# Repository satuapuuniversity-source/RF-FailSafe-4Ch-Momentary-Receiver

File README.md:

This project is a smart RF receiver board made for things like quiz buzzers, remote switches, or simple automation systems.

Normally, RF receivers can have a problem:
👉 if the signal suddenly stops, the output can get “stuck” ON.
That’s bad, especially in real applications.

So I fixed that.

This board uses a small logic chip (74HC08) to make sure:
✔ the output turns ON only when a signal is actually present
✔ and turns OFF instantly when the signal is gone

So everything works clean and momentary—just like pressing a button.

Another cool thing is the RCA outputs.
They work like simple switches (dry contact), not powered outputs.

👉 That means you can safely connect this board to other systems without worrying about voltage mismatch.

Each channel also has:
💡 a small LED
🔁 a sensing loop (10k resistor)

So you can see if your external device is connected and working. Super helpful during setup.

For power, it runs on a single 18650 battery, and a boost converter keeps everything stable at 5V.
So it’s portable and reliable.

And the PCB?
Designed in KiCad with clear labels, so it’s easy to install and use, even if you're not an expert.

👉 In short:
This is a safe, reliable, no-glitch RF receiver that behaves exactly how you expect—no stuck signals, no confusion.

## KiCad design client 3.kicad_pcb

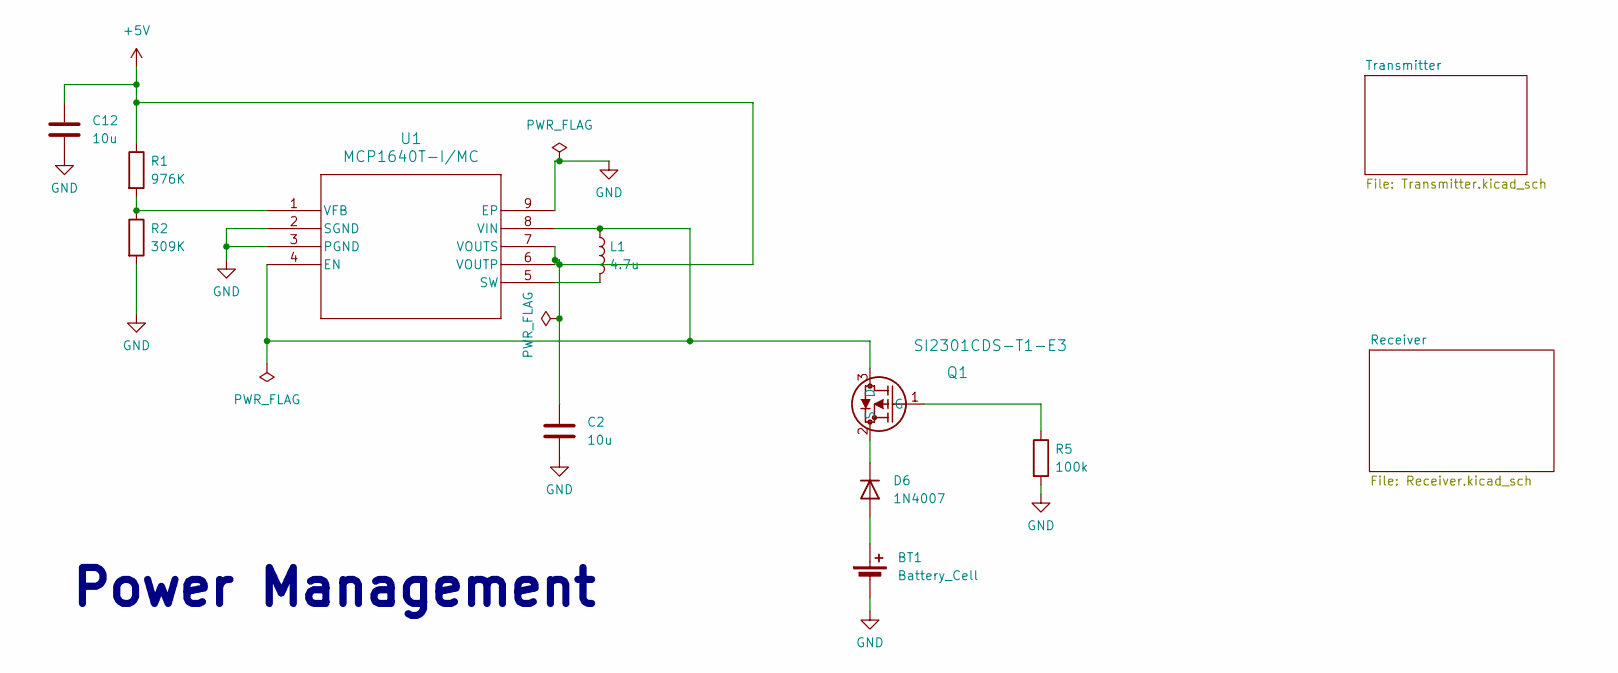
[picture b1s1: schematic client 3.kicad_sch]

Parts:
BT1: Battery_Cell; BatteryHolder_Keystone_1042_1x18650
C2, C12: 10u; C_0805_2012Metric
D6: 1N4007; D_DO-41_SOD81_P10.16mm_Horizontal
L1: 4.7u; R_0805_2012Metric
Q1: SI2301CDS-T1-E3; SOT-23
R1: 976K; R_0805_2012Metric
R2: 309K; R_0805_2012Metric
R5: 100k; R_0805_2012Metric
U1: MCP1640T-I/MC; DFN-8-1EP_2x3mm_P0.5mm_EP0.61x2.2mm

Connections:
GND: BT1.2 (-), C2.2, C12.2, R2.2, R5.2, U1.2 (SGND), U1.3 (PGND), U1.9 (EP); also elsewhere on the board
unnamed: BT1.1 (+), D6.2 (A)
unnamed: D6.1 (K), Q1.2 (S)
unnamed: L1.1, Q1.3 (D), U1.4 (EN), U1.8 (VIN)
unnamed: Q1.1 (G), R5.1
unnamed: L1.2, U1.5 (SW)
unnamed: R1.2, R2.1, U1.1 (VFB)

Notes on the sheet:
Power Management

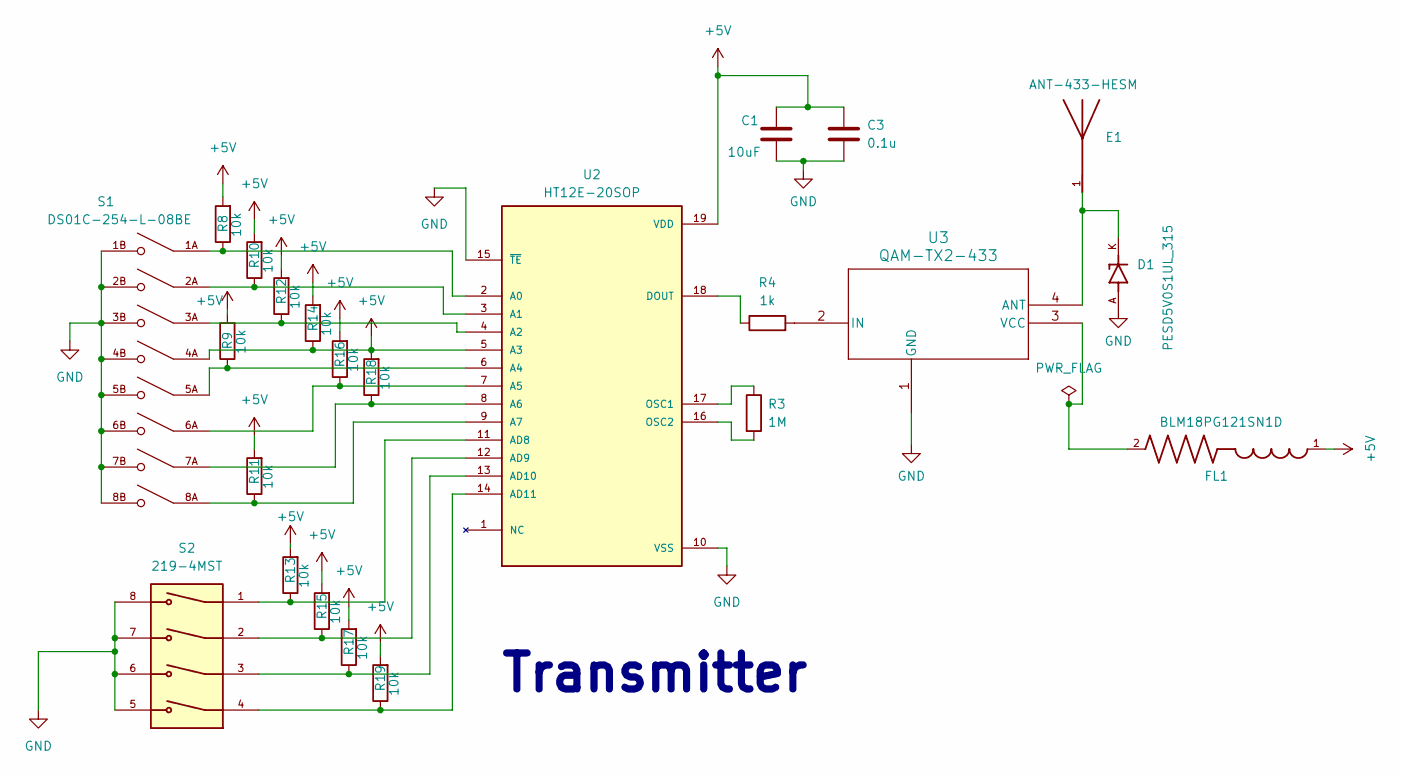
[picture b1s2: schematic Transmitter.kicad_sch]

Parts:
C1: 10uF; C_0805_2012Metric
C3: 0.1u; C_0603_1608Metric
D1: PESD5V0S1UL_315; DIO_PESD5V0S1UL_315
E1: ANT-433-HESM; XDCR_ANT-433-HESM; PARTREV B
FL1: BLM18PG121SN1D; BEADC1608X95N
R3: 1M; R_0805_2012Metric
R4: 1k; R_0805_2012Metric
R8, R9, R10, R11, R12, R13, R14, R15, R16, R17, R18, R19: 10k; R_0805_2012Metric
S1: DS01C-254-L-08BE; SW_DS01C-254-L-08BE; PARTREV 1.0
S2: 219-4MST; SW_219-4MST; PARTREV C
U2: HT12E-20SOP; SOP127P1032X264-20N; PARTREV 1.1
U3: QAM-TX2-433; QAM-TX2-433_RFS

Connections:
GND: C1.2, C3.2, D1.A, S1.1B, S1.2B, S1.3B, S1.4B, S1.5B, S1.6B, S1.7B, S1.8B, S2.5, S2.6, S2.7, S2.8, U2.10 (VSS), U2.15 (~TE), U3.1 (GND); also elsewhere on the board
unnamed: R8.1, S1.1A, U2.2 (A0)
unnamed: R10.1, S1.2A, U2.3 (A1)
unnamed: R12.1, S1.3A, U2.4 (A2)
unnamed: R9.1, S1.5A, U2.6 (A4)
unnamed: R16.1, S1.6A, U2.7 (A5)
unnamed: R18.1, S1.7A, U2.8 (A6)
unnamed: R11.1, S1.8A, U2.9 (A7)
unnamed: R13.1, S2.1, U2.11 (AD8)
unnamed: R15.1, S2.2, U2.12 (AD9)
unnamed: R17.1, S2.3, U2.13 (AD10)
unnamed: R19.1, S2.4, U2.14 (AD11)
unnamed: R4.1, U2.18 (DOUT)
unnamed: R3.1, U2.17 (OSC1)
unnamed: R3.2, U2.16 (OSC2)
unnamed: D1.K, E1.1, U3.4 (ANT)
unnamed: R4.2, U3.2 (IN)
unnamed: FL1.2, U3.3 (VCC)

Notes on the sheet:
Transmitter

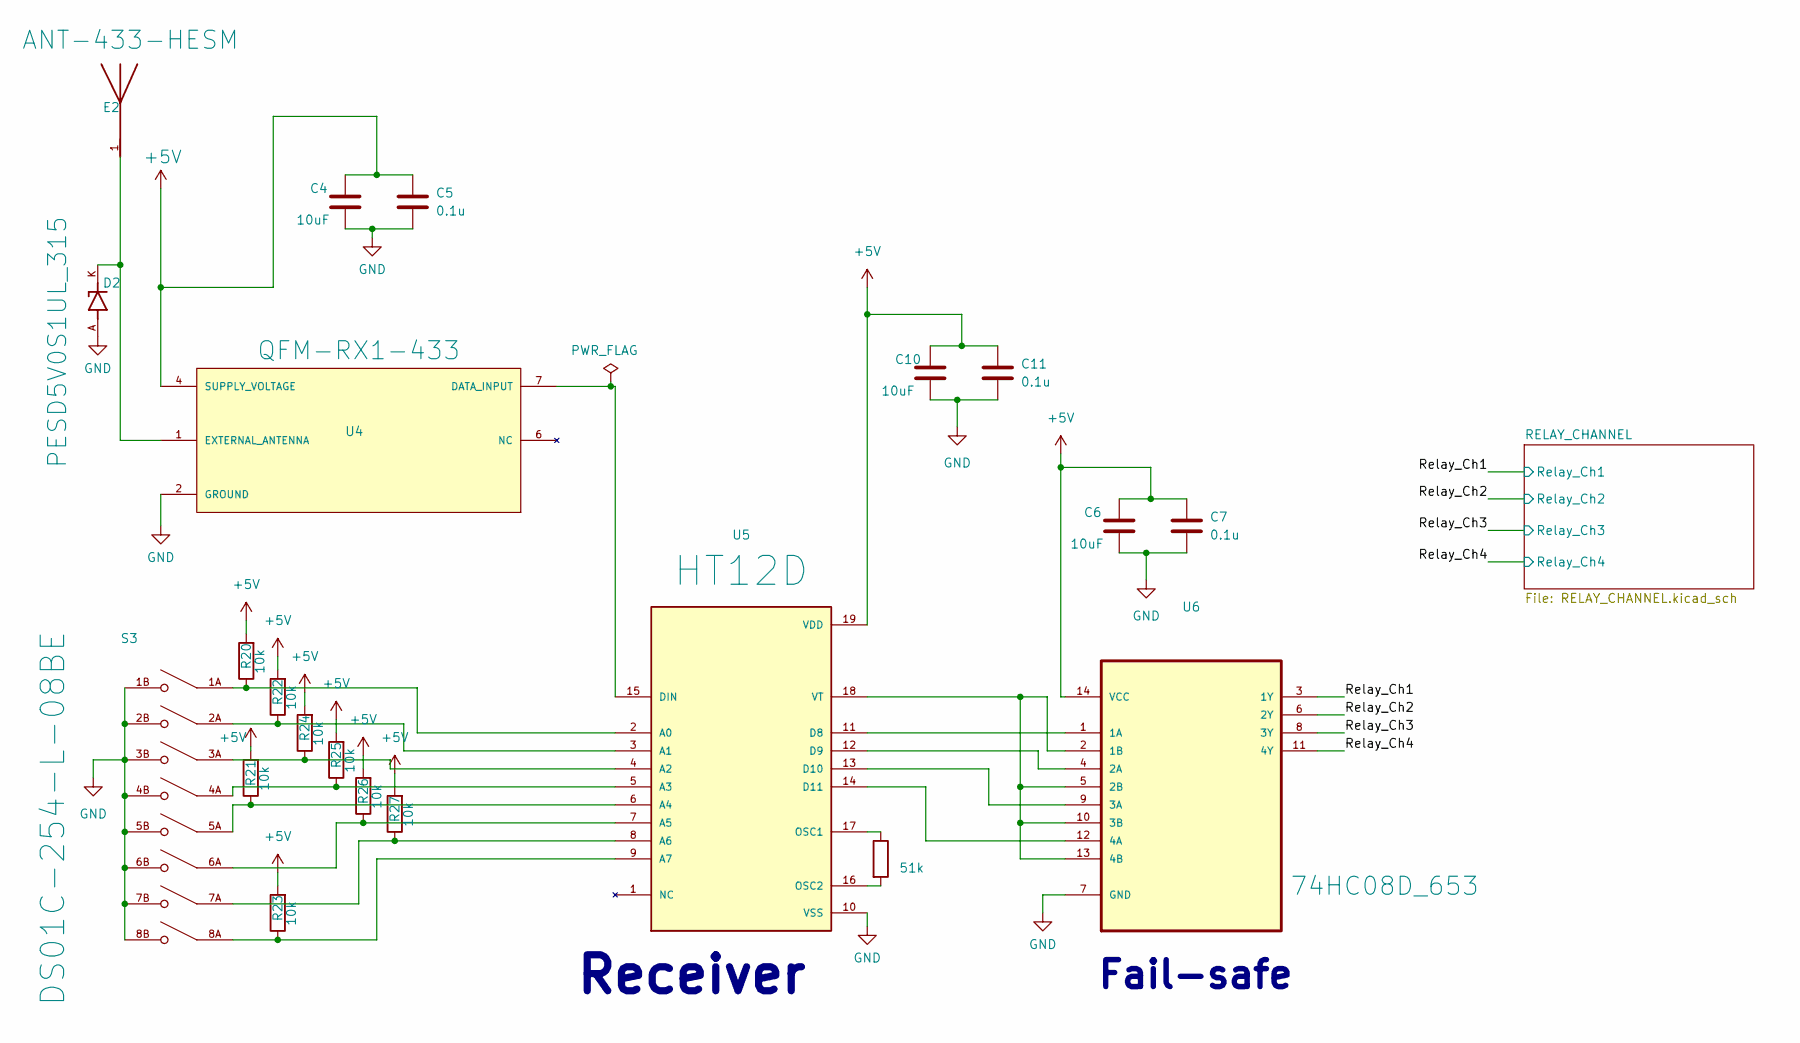
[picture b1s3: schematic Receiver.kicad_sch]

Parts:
C4, C6, C10: 10uF; C_0805_2012Metric
C5, C7, C11: 0.1u; C_0603_1608Metric
D2: PESD5V0S1UL_315; DIO_PESD5V0S1UL_315
E2: ANT-433-HESM; XDCR_ANT-433-HESM; PARTREV B
R6: 51k; R_0805_2012Metric
R20, R21, R22, R23, R24, R25, R26, R27: 10k; R_0805_2012Metric
S3: DS01C-254-L-08BE; SW_DS01C-254-L-08BE; PARTREV 1.0
U4: QFM-RX1-433; MODULE_QFM-RX1-433; PARTREV March 14
U5: HT12D; SOP127P1032X264-20N; PARTREV 1.4
U6: 74HC08D_653; SOIC127P600X175-14N; MPN 74HC08D,653

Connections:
/Receiver/Relay_Ch1: U6.3 (1Y); also elsewhere on the board
/Receiver/Relay_Ch2: U6.6 (2Y); also elsewhere on the board
/Receiver/Relay_Ch3: U6.8 (3Y); also elsewhere on the board
/Receiver/Relay_Ch4: U6.11 (4Y); also elsewhere on the board
GND: C4.2, C5.2, C6.2, C7.2, C10.2, C11.2, D2.A, S3.1B, S3.2B, S3.3B, S3.4B, S3.5B, S3.6B, S3.7B, S3.8B, U4.2 (GROUND), U4.3 (GROUND), U4.8 (GROUND), U5.10 (VSS), U6.7 (GND); also elsewhere on the board
unnamed: U4.7 (DATA_INPUT), U5.15 (DIN)
unnamed: D2.K, E2.1, U4.1 (EXTERNAL_ANTENNA)
unnamed: R20.1, S3.1A, U5.2 (A0)
unnamed: R22.1, S3.2A, U5.3 (A1)
unnamed: R24.1, S3.3A, U5.4 (A2)
unnamed: R25.1, S3.4A, U5.5 (A3)
unnamed: R21.1, S3.5A, U5.6 (A4)
unnamed: R26.1, S3.6A, U5.7 (A5)
unnamed: R27.1, S3.7A, U5.8 (A6)
unnamed: R23.1, S3.8A, U5.9 (A7)
unnamed: U5.11 (D8), U6.1 (1A)
unnamed: U5.12 (D9), U6.4 (2A)
unnamed: U5.13 (D10), U6.9 (3A)
unnamed: U5.14 (D11), U6.12 (4A)
unnamed: R6.1, U5.17 (OSC1)
unnamed: R6.2, U5.16 (OSC2)
unnamed: U5.18 (VT), U6.2 (1B), U6.5 (2B), U6.10 (3B), U6.13 (4B)

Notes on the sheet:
Fail-safe
Receiver

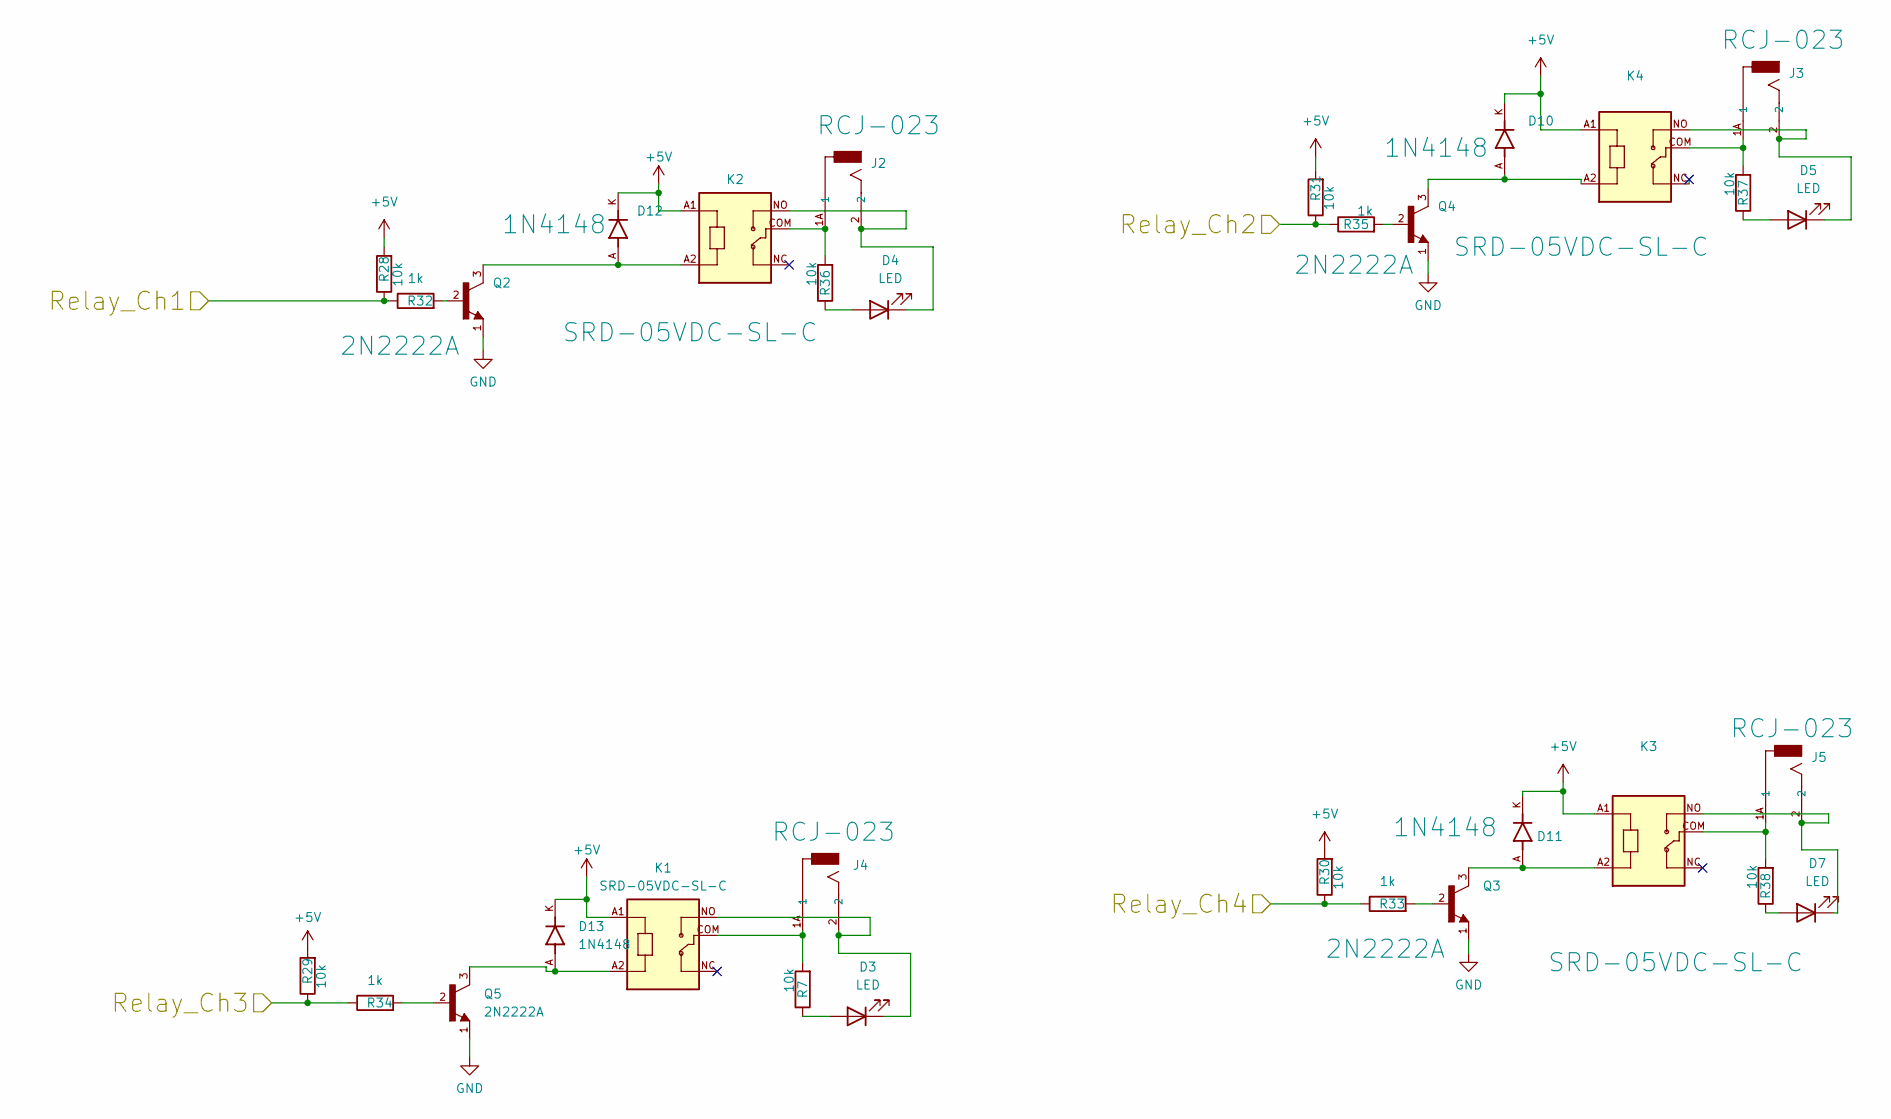
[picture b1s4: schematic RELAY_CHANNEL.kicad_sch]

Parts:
D3, D4, D5, D7: LED; LED_0805_2012Metric
D10, D11, D12, D13: 1N4148; DIOAD753W49L380D172B; PARTREV 5
J2, J3, J4, J5: RCJ-023; CUI_RCJ-023; PART_REV B
K1, K2, K3, K4: SRD-05VDC-SL-C; RELAY_SRD-05VDC-SL-C
Q2, Q3, Q4, Q5: 2N2222A; TO127P584H533-3; PARTREV 2
R7, R28, R29, R30, R31, R36, R37, R38: 10k; R_0805_2012Metric
R32, R33, R34, R35: 1k; R_0805_2012Metric

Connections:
/Receiver/Relay_Ch1: R28.1, R32.1; also elsewhere on the board
/Receiver/Relay_Ch2: R31.1, R35.1; also elsewhere on the board
/Receiver/Relay_Ch3: R29.1, R34.1; also elsewhere on the board
/Receiver/Relay_Ch4: R30.1, R33.1; also elsewhere on the board
GND: Q2.1, Q3.1, Q4.1, Q5.1; also elsewhere on the board
unnamed: D3.2 (A), R7.1
unnamed: D3.1 (K), J4.2, K1.NO
unnamed: D4.2 (A), R36.1
unnamed: D4.1 (K), J2.2, K2.NO
unnamed: D5.2 (A), R37.1
unnamed: D5.1 (K), J3.2, K4.NO
unnamed: D7.2 (A), R38.1
unnamed: D7.1 (K), J5.2, K3.NO
unnamed: D10.A, K4.A2, Q4.3
unnamed: D11.A, K3.A2, Q3.3
unnamed: D12.A, K2.A2, Q2.3
unnamed: D13.A, K1.A2, Q5.3
unnamed: J2.1A (1), J2.1B (1), K2.COM, R36.2
unnamed: J3.1A (1), J3.1B (1), K4.COM, R37.2
unnamed: J4.1A (1), J4.1B (1), K1.COM, R7.2
unnamed: J5.1A (1), J5.1B (1), K3.COM, R38.2
unnamed: Q2.2, R32.2
unnamed: Q3.2, R33.2
unnamed: Q4.2, R35.2
unnamed: Q5.2, R34.2

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
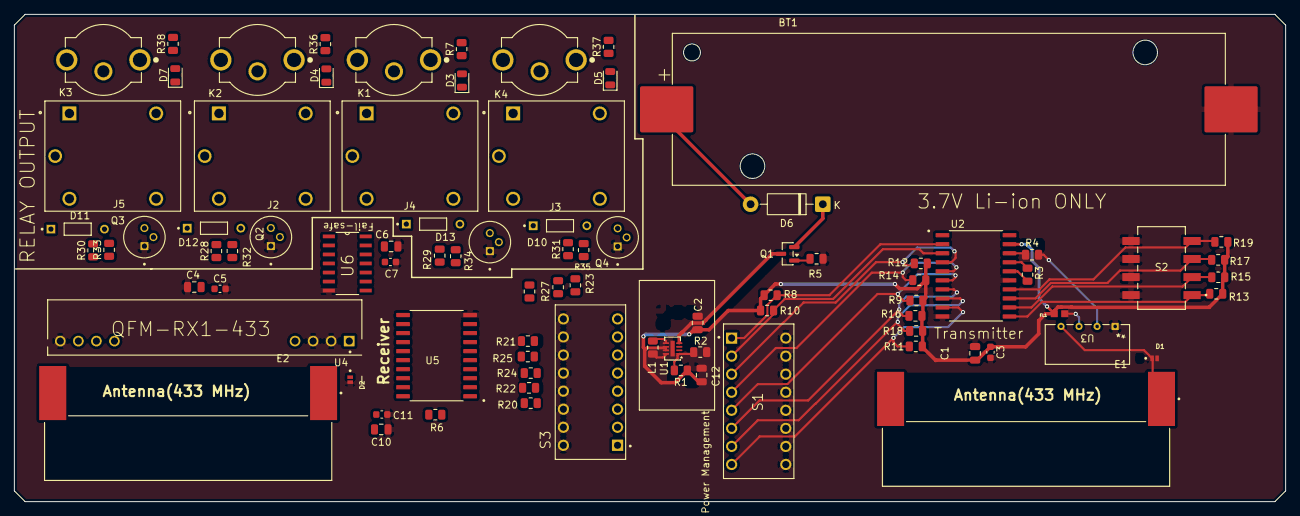
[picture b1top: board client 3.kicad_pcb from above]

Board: 2 copper layers, 178.8 x 68.5 mm, 86 parts (0 on the bottom side), 67 nets.

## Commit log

2026-05-01 3d view
    Expanded project description and added details about functionality and features.
